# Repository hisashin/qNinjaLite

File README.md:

# Open Source $50 qLAMP machine qNinja

# $300 Real Time PCR and LAMP machine "[qNinja](https://github.com/hisashin/qNinja)" is also available

## Reference Links
- [qNinja portal](https://qninja.hisa.dev)

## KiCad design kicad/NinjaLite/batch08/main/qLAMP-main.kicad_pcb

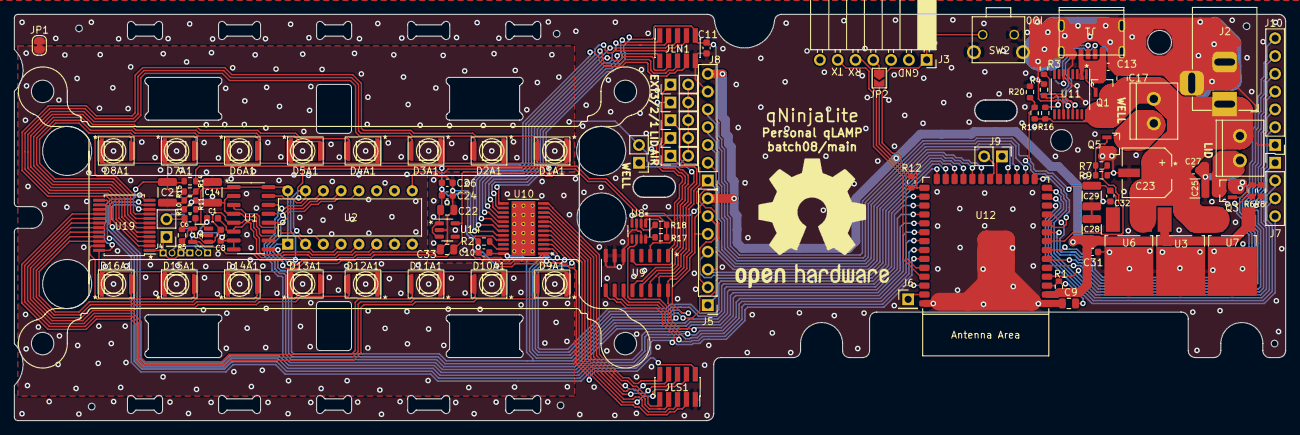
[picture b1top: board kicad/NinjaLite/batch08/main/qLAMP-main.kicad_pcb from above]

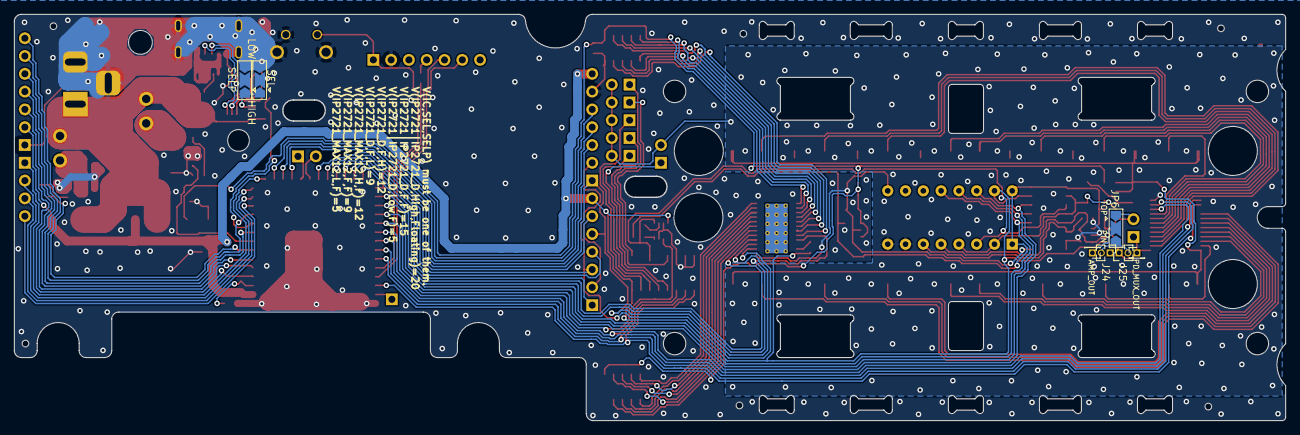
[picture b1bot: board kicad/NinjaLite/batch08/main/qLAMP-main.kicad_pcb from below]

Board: 2 copper layers, 181.5 x 58.0 mm, 102 parts (7 on the bottom side), 104 nets.

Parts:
C1, C10, C11, C24, C27, C31, C32: 0.1uF; C_0603_1608Metric
C2, C14, C25, C28, C29: 22uF; C_1210_3225Metric
C6: 5pF; C_0603_1608Metric
C8: DNP; C_0603_1608Metric
C9: 10uF; C_0805_2012Metric
C13: 1uF(<=20V); C_0603_1608Metric
C17: 10uF(<=20V); C_0805_2012Metric
C22, C33: 4.7uF; C_0805_2012Metric
C23: 100uF; 35TZV100M6.3X8
C26: 0.01uF; C_0603_1608Metric
D1A1, D2A1, D3A1, D4A1, D5A1, D6A1, D7A1, D8A1, D9A1, D10A1, D11A1, D12A1, D13A1, D14A1, D15A1, D16A1: D_Photo; SFH2200_2201_2240
HLID1: Screw_Terminal_01x02; TB_SeeedOPL_320110028
HWELL1: Screw_Terminal_01x02; TB_SeeedOPL_320110028
J1: ALI_USB
J2: Barrel_Jack_Switch; BarrelJack_Horizontal
J3: Conn_01x07_Male; PinSocket_1x07_P2.54mm_Horizontal
J4: Conn_01x02_Male; PinHeader_1x02_P2.54mm_Vertical
J5, J8: Conn_01x07_Male; PinHeader_1x07_P2.54mm_Vertical
J6: Conn_01x01_Pin; PinHeader_1x01_P2.54mm_Vertical
J7: Conn_01x04_Male; PinHeader_1x04_P2.54mm_Vertical
J9: Conn_01x02_Pin; PinHeader_1x02_P2.54mm_Vertical
J10: Conn_01x07_Pin; PinHeader_1x07_P2.54mm_Vertical
J13, J16: Conn_01x01_Male; PinHeader_1x01_P1.27mm_Vertical
J24, J25: Conn_01x02_Male; PinHeader_1x02_P1.27mm_Vertical
JLN1: Conn_01x10_Male; PinSocket_2x05_P1.27mm_Vertical_SMD
JLS1: Conn_01x10_Male; PinSocket_2x05_P1.27mm_Vertical_SMD
JP1: SolderJumper_2_Bridged; SolderJumper-2_P1.3mm_Bridged_RoundedPad1.0x1.5mm
JP2: Jumper_2_Bridged; SolderJumper-2_P1.3mm_Open_TrianglePad1.0x1.5mm
JP6, JP9, JP10: Jumper_3_Open; SolderJumper-3_P2.0mm_Open_TrianglePad1.0x1.5mm
Q1, Q3, Q5: Q_NMOS_GSD; SOT95P240X112-3N
R1, R12, R15, R16, R19: 100k; R_0603_1608Metric
R2: 3.3k; R_0603_1608Metric
R3, R4: 5.1k; R_0603_1608Metric
R5: 10M; R_0603_1608Metric
R6, R7: 150; R_0603_1608Metric
R8, R9: 47k; R_0603_1608Metric
R10, R11, R18: 47k_HP; R_0603_1608Metric
R14, R20: 10k; R_0603_1608Metric
R17: 10k_HP; R_0603_1608Metric
SW2: TACTILE_4; SW_TH_Tactile_alps_SKHHLPA010
TAIR1: Conn_01x02_Male; PinHeader_1x02_P2.54mm_Vertical
TEXT1, TEXT2, TEXT3: Conn_01x02_Male; PinHeader_1x02_P2.54mm_Vertical
TLID1: Conn_01x02_Male; PinHeader_1x02_P2.54mm_Vertical
TWELL1: Conn_01x02_Male; PinHeader_1x02_P2.54mm_Vertical
U1: NAU7802; SOIC-16_3.9x9.9mm_P1.27mm
U2: NAU7802; DIP-16_W7.62mm
U3: BD433M5FP-CE2; REG_TO252-3
U4: LMP7717MF_NOPB; SOT-23-5
U6: BA178M05FP-E2; REG_TO252-3
U7: BD433M5FP-CE2; REG_TO252-3-INV
U8: TS12A12511DCNR; SOT-23-8-8.3mil
U9: SN74LV4051A; SOIC-16_3.9x9.9mm_P1.27mm
U10: TLC5929; HTSSOP-24-1EP_4.4x7.8mm_P0.65mm_EP3.4x7.8mm_Mask2.4x4.68mm_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
U11: IP2721; TSSOP-16_4.4x5mm_P0.65mm
U12: ESP32-­S3-­WROOM­-1; ESP32-S3-WROOM-1
U14: TCR3DF33,LM(CT; SOT-23-5
U19: CD74HC4067M96; SSOP-24_5.3x8.2mm_P0.65mm-0.83mil

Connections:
3V3A: C33.1, R10.1, R17.1, R18.1, U1.1 (REFP), U1.16 (AVDD), U2.1 (REFP), U2.16 (AVDD), U4.3 (IN+), U14.5 (VOUT)
3V3D: C10.1, C28.1, C31.1, J5.7, J8.7, J10.2, JP2.2 (B), R1.2, R12.2, U1.15 (DVDD), U2.15 (DVDD), U3.2 (VOUT), U4.5 (V+), U7.2 (VOUT), U8.4 (V+), U9.16 (VCC), U10.24 (VCC), U12.2 (3V3)
5V: C11.1, C22.1, C24.1, C26.1, C29.1, C32.1, JLN1.9, JLS1.2, R14.1, U6.2 (VOUT), U14.1 (VIN), U14.3 (SHDN)
/BOOTMODE: J3.1, R12.1, SW2.1, U12.27 (IO0)
/IO1: J6.1, U12.39 (IO1)
/IO4: J10.3, U12.4 (IO4)
/IO5: J10.4, U12.5 (IO5)
/IO6: J10.5, U12.6 (IO6)
/IO11: J9.1, U12.19 (IO11)
/IO12: J9.2, U12.20 (IO12)
/IO16: J10.6, U12.9 (IO16)
/IO18: J10.7, U12.11 (IO18)
/LCD_CS: J8.5, U12.16 (IO46)
/LCD_DC/RS: J8.3, U12.18 (IO10)
/LCD_RESET: J8.4, U12.17 (IO9)
/LID_HEATER: R6.2, U12.7 (IO7)
/MISO: J5.2, J5.6, U12.22 (IO14)
/Photo/AMP_OUT: C8.1, J16.1, JP6.2 (C), U1.5 (VIN2P), U2.5 (VIN2P), U4.1 (OUT)
/Photo/VBG: C1.1, U1.6 (VBG), U2.6 (VBG)
/PhotoLED/N_LED_OUT1: JLN1.8, U10.20 (OUT15)
/PhotoLED/N_LED_OUT2: JLN1.7, U10.19 (OUT14)
/PhotoLED/N_LED_OUT3: JLN1.6, U10.18 (OUT13)
/PhotoLED/N_LED_OUT4: JLN1.5, U10.17 (OUT12)
/PhotoLED/N_LED_OUT5: JLN1.4, U10.16 (OUT11)
/PhotoLED/N_LED_OUT6: JLN1.3, U10.15 (OUT10)
/PhotoLED/N_LED_OUT7: JLN1.2, U10.14 (OUT9)
/PhotoLED/N_LED_OUT8: JLN1.1, U10.13 (OUT8)
/PhotoLED/S_LED_OUT1: JLS1.3, U10.5 (OUT0)
/PhotoLED/S_LED_OUT2: JLS1.4, U10.6 (OUT1)
/PhotoLED/S_LED_OUT3: JLS1.5, U10.7 (OUT2)
/PhotoLED/S_LED_OUT4: JLS1.6, U10.8 (OUT3)
/PhotoLED/S_LED_OUT5: JLS1.7, U10.9 (OUT4)
/PhotoLED/S_LED_OUT6: JLS1.8, U10.10 (OUT5)
/PhotoLED/S_LED_OUT7: JLS1.9, U10.11 (OUT6)
/PhotoLED/S_LED_OUT8: JLS1.10, U10.12 (OUT7)
/PhotoMUX/N_PD_OUT1: D1A1.2 (A), U19.2 (I7)
/PhotoMUX/N_PD_OUT3: D2A1.2 (A), U19.3 (I6)
/PhotoMUX/N_PD_OUT5: D3A1.2 (A), U19.4 (I5)
/PhotoMUX/N_PD_OUT7: D4A1.2 (A), U19.5 (I4)
/PhotoMUX/N_PD_OUT9: D5A1.2 (A), U19.6 (I3)
/PhotoMUX/N_PD_OUT11: D6A1.2 (A), U19.7 (I2)
/PhotoMUX/N_PD_OUT13: D7A1.2 (A), U19.8 (I1)
/PhotoMUX/N_PD_OUT15: D8A1.2 (A), U19.9 (I0)
/PhotoMUX/S_PD_OUT1: D9A1.2 (A), U19.16 (I15)
/PhotoMUX/S_PD_OUT3: D10A1.2 (A), U19.17 (I14)
/PhotoMUX/S_PD_OUT5: D11A1.2 (A), U19.18 (I13)
/PhotoMUX/S_PD_OUT7: D12A1.2 (A), U19.19 (I12)
/PhotoMUX/S_PD_OUT9: D13A1.2 (A), U19.20 (I11)
/PhotoMUX/S_PD_OUT11: D14A1.2 (A), U19.21 (I10)
/PhotoMUX/S_PD_OUT13: D15A1.2 (A), U19.22 (I9)
/PhotoMUX/S_PD_OUT15: D16A1.2 (A), U19.23 (I8)
/Power/SEL: JP9.2 (C), U11.11 (SEL)
/Power/SELP: JP10.2 (C), U11.6 (SELP)
/Power/VIN: C13.1, J1.A9 (VBUS), J1.B9 (VBUS), Q1.3 (D), U11.2 (VIN)
/RXD: J3.5, U12.36 (IO44/RXD0)
/SD_CLK: J7.4, U12.12 (IO8)
/SD_CS: J7.1, U12.15 (IO3)
/SD_MISO: J7.3, U12.13 (IO19)
/SD_MOSI: J7.2, U12.14 (IO20)
/TP_CS: J5.4, U12.24 (IO47)
/TP_IRQ: J5.1, U12.25 (IO48)
/TXD: J3.6, U12.37 (IO43/TXD0)
/WELL_HEATER: R7.2, U12.8 (IO15)
DIVIDED: C14.1, R10.2, R11.1, U1.2 (VIN1N), U1.4 (VIN2N), U2.2 (VIN1N), U2.4 (VIN2N)
GNDA: C1.2, C2.2, C8.2, C14.2, JP1.2 (B), R11.2, R15.2, TAIR1.2, TEXT1.2, TEXT2.2, TEXT3.2, TLID1.2, TWELL1.2, U1.7 (REFN), U1.8 (AVSS), U2.7 (REFN), U2.8 (AVSS), U4.2 (V-), U19.12 (GND), U19.15 (*E)
GNDD: C9.2, C10.2, C11.2, C13.2, C17.2, C22.2, C23.2, C24.2, C25.2, C26.2, C27.2, C28.2, C29.2, C31.2, C32.2, C33.2, J1.A12 (GND), J1.B12 (GND), J1.S1 (SHELD1), J1.S2 (SHELD2), J1.S3 (SHELD3), J1.S4 (SHELD4), J2.2, J2.3, J3.2, J8.6, J10.1, JLN1.10, JLS1.1, JP1.1 (A), JP9.3 (B), JP10.3 (B), Q3.2 (S), Q5.2 (S), R2.2, R3.1, R4.1, R8.1, R9.1, R20.2, SW2.2, SW2.GND, U1.9 (DVSS), U2.9 (DVSS), U3.3 (GND), U6.3 (GND), U7.3 (GND), U8.3 (GND), U8.7 (V-), U9.6 (INH), U9.7 (GND), U9.8 (GND), U10.1 (GND), U11.5 (GND), U12.1 (GND), U12.40 (GND), U12.41 (GND), U14.2 (GND)
I2C_SCL: U1.13 (SCLK), U2.13 (SCLK), U12.30 (IO37)
I2C_SDA: U1.14 (SDIO), U2.14 (SDIO), U12.31 (IO38)
LED_BLANK: U10.21 (BLANK), U12.28 (IO35)
LED_LAT: U10.4 (LAT), U12.26 (IO45)
MOSI: J5.3, J8.2, U10.2 (SIN), U12.23 (IO21)
MUX_S0: U9.11 (A), U12.33 (IO40), U19.10 (S0)
MUX_S1: U9.10 (B), U12.35 (IO42), U19.11 (S1)
MUX_S2: U9.9 (C), U12.38 (IO2), U19.14 (S2)
MUX_S3: U12.34 (IO41), U19.13 (S3)
NAU_DRDY: U1.12 (DRDY), U2.12 (DRDY), U12.29 (IO36)
unnamed: HLID1.2, Q3.3 (D)
unnamed: HWELL1.2, Q5.3 (D)
unnamed: J1.A5 (CC1), R3.2, U11.13 (CC1)
unnamed: J1.B5 (CC2), R4.2, U11.12 (CC2)
unnamed: J3.4, JP2.1 (A)
unnamed: C6.1, J4.2, JP6.1 (A), R5.2
unnamed: J24.2, J25.2, JP6.3 (B)
unnamed: JP9.1 (A), JP10.1 (A), R16.1
unnamed: Q1.1 (G), U11.1 (VBUSG)
unnamed: Q3.1 (G), R6.1, R8.2
unnamed: Q5.1 (G), R7.1, R9.2
unnamed: R18.2, U8.2 (NC)
unnamed: R17.2, U8.8 (NO)
unnamed: R2.1, U10.23 (IREF)
unnamed: C9.1, R1.1, U12.3 (EN)
PD_MUX_OUT: C6.2, J4.1, J13.1, J24.1, J25.1, R5.1, U4.4 (IN-), U19.1 (COMMONINPUT/OUTPUT)
SCLK: J5.5, J8.1, U10.3 (SCLK), U12.21 (IO13)
THERM_AIR: TAIR1.1, U9.14 (Y1)
THERM_EXT1: TEXT1.1, U9.15 (Y2)
THERM_EXT2: TEXT2.1, U9.1 (Y4)
THERM_EXT3: TEXT3.1, U9.5 (Y5)
THERM_LID: TLID1.1, U9.12 (Y3)
THERM_MUX_OUT: U1.3 (VIN1P), U2.3 (VIN1P), U8.1 (COM), U9.3 (COM)
THERM_R_SWITCH: U8.6 (IN), U12.32 (IO39)
THERM_WELL: TWELL1.1, U9.13 (Y0)
VCC: C17.1, C23.1, C25.1, C27.1, HLID1.1, HWELL1.1, J2.1, Q1.2 (S), R16.2, R19.1, U3.1 (VIN), U6.1 (VIN), U7.1 (VIN), U11.16 (VBUS)
VIN_SENSE: R19.2, R20.1, U12.10 (IO17)
VOPT: C2.1, D1A1.1 (K), D2A1.1 (K), D3A1.1 (K), D4A1.1 (K), D5A1.1 (K), D6A1.1 (K), D7A1.1 (K), D8A1.1 (K), D9A1.1 (K), D10A1.1 (K), D11A1.1 (K), D12A1.1 (K), D13A1.1 (K), D14A1.1 (K), D15A1.1 (K), D16A1.1 (K), R14.2, R15.1, U19.24 (VCC)

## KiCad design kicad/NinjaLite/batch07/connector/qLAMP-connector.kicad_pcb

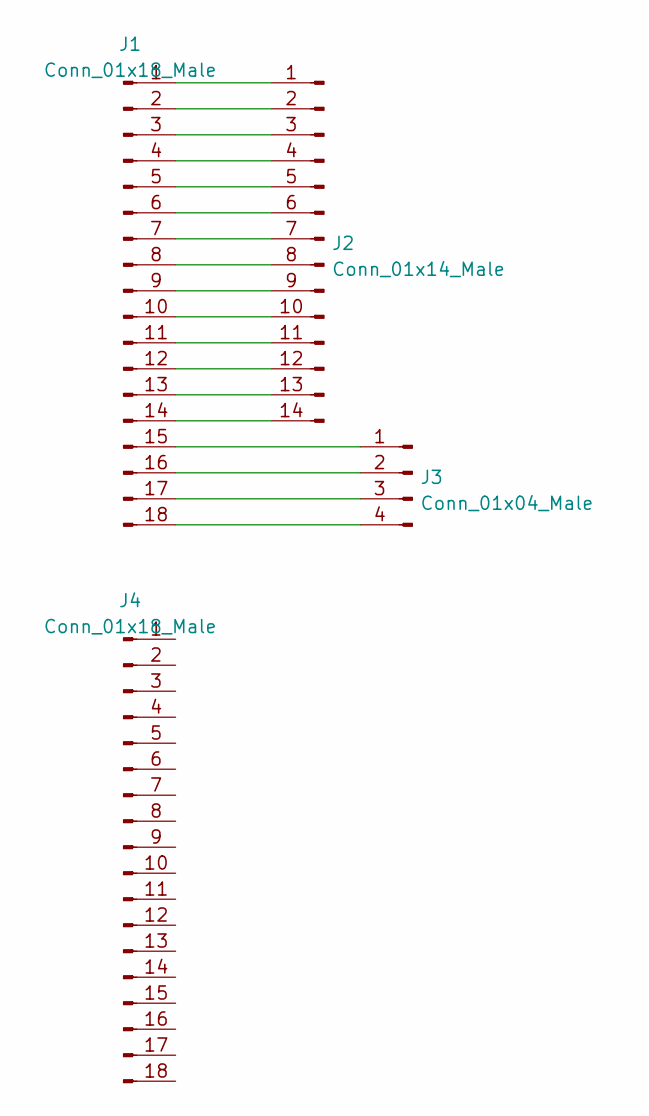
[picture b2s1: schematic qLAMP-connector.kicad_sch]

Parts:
J1: Conn_01x18_Male; PinSocket_2x09_P2.54mm_Vertical
J2: Conn_01x14_Male; PinSocket_1x14_P2.54mm_Vertical
J3: Conn_01x04_Male; PinSocket_1x04_P2.54mm_Vertical
J4: Conn_01x18_Male; PinSocket_2x09_P1.27mm_Vertical

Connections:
unnamed: J1.1, J2.1
unnamed: J1.2, J2.2
unnamed: J1.3, J2.3
unnamed: J1.4, J2.4
unnamed: J1.5, J2.5
unnamed: J1.6, J2.6
unnamed: J1.7, J2.7
unnamed: J1.8, J2.8
unnamed: J1.9, J2.9
unnamed: J1.10, J2.10
unnamed: J1.11, J2.11
unnamed: J1.12, J2.12
unnamed: J1.13, J2.13
unnamed: J1.14, J2.14
unnamed: J1.15, J3.1
unnamed: J1.16, J3.2
unnamed: J1.17, J3.3
unnamed: J1.18, J3.4

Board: 2 copper layers, 4 parts (0 on the bottom side), 18 nets, no tracks yet.

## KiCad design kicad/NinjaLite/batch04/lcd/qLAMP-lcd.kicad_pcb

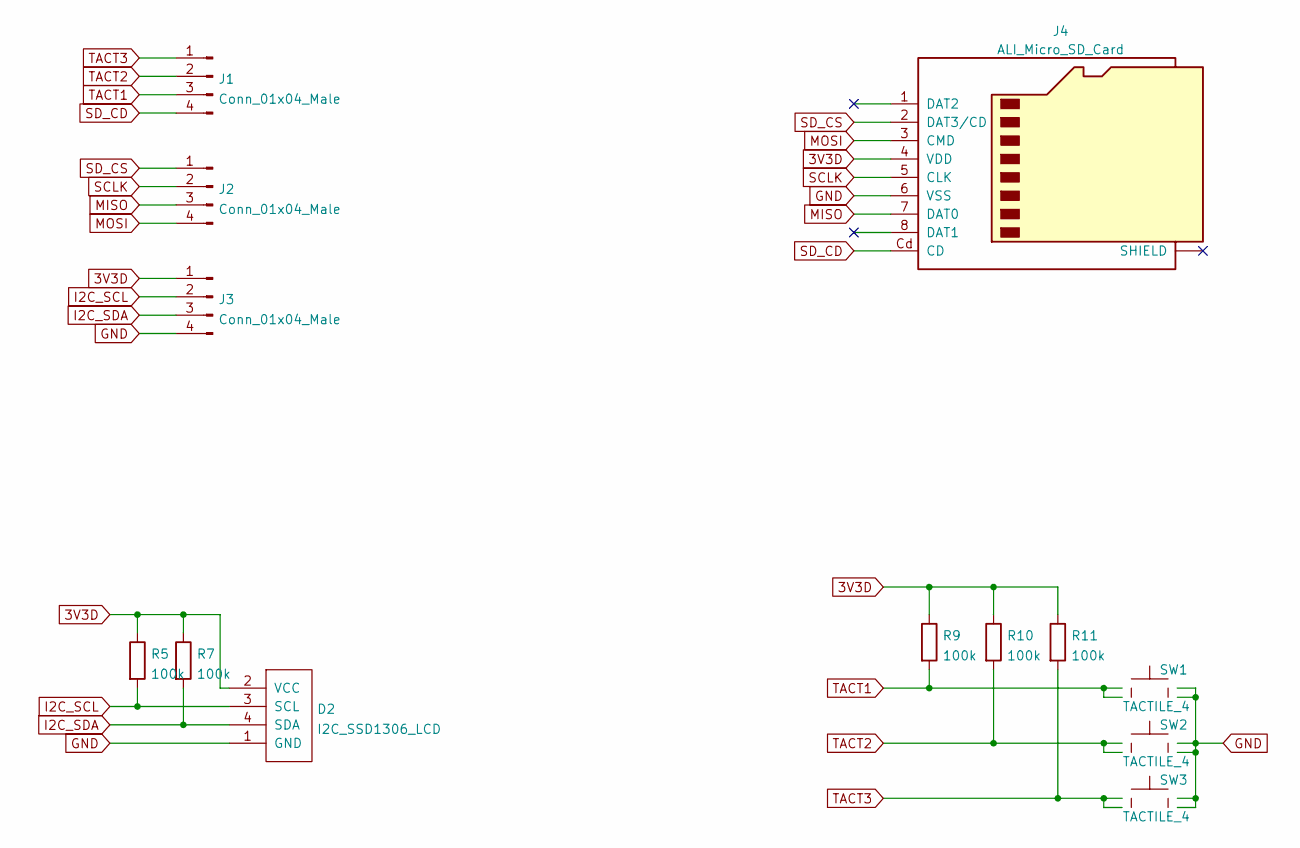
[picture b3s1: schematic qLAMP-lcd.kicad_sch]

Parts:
D2: I2C_SSD1306_LCD; ALI_I2C_LCD
J1, J2, J3: Conn_01x04_Male; PinHeader_1x04_P2.54mm_Vertical
J4: ALI_Micro_SD_Card; ALI_microSD
R5, R7, R9, R10, R11: 100k; R_0603_1608Metric
SW1, SW2, SW3: TACTILE_4; SW_TH_Tactile_Omron_B3F-10xx

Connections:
3V3D: D2.2 (VCC), J3.1, J4.4 (VDD), R5.1, R7.1, R9.1, R10.1, R11.1
GND: D2.1 (GND), J3.4, J4.6 (VSS), SW1.3, SW1.4, SW2.3, SW2.4, SW3.3, SW3.4
I2C_SCL: D2.3 (SCL), J3.2, R5.2
I2C_SDA: D2.4 (SDA), J3.3, R7.2
MISO: J2.3, J4.7 (DAT0)
MOSI: J2.4, J4.3 (CMD)
SCLK: J2.2, J4.5 (CLK)
SD_CD: J1.4, J4.Cd (CD)
SD_CS: J2.1, J4.2 (DAT3/CD)
TACT1: J1.3, R9.2, SW1.1, SW1.2
TACT2: J1.2, R10.2, SW2.1, SW2.2
TACT3: J1.1, R11.2, SW3.1, SW3.2

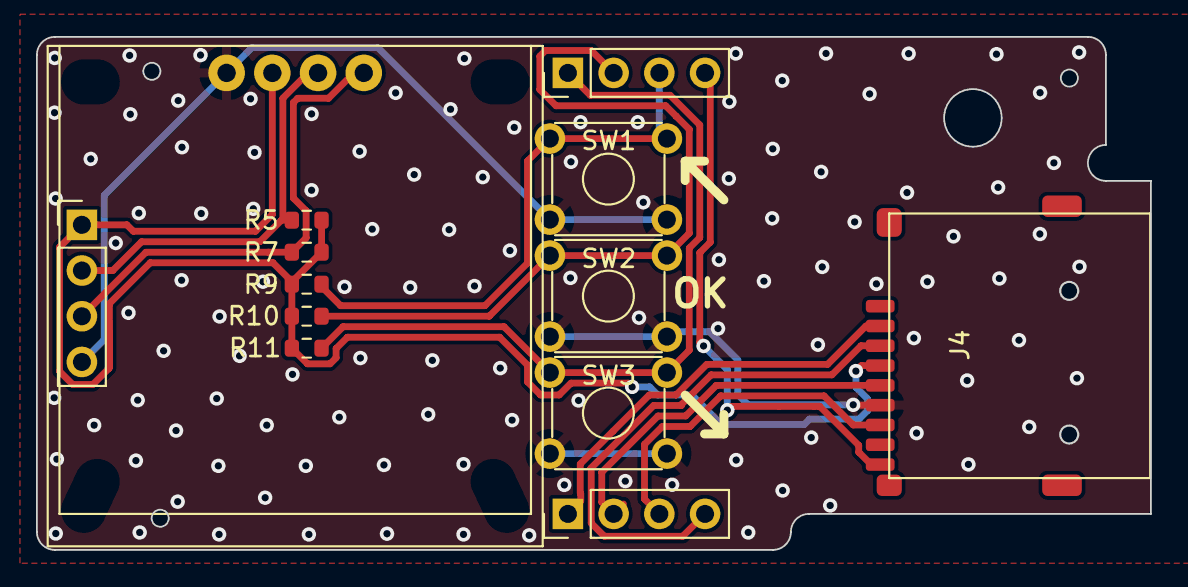
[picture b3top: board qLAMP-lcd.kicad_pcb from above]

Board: 2 copper layers, 61.9 x 28.5 mm, 13 parts (0 on the bottom side), 12 nets.

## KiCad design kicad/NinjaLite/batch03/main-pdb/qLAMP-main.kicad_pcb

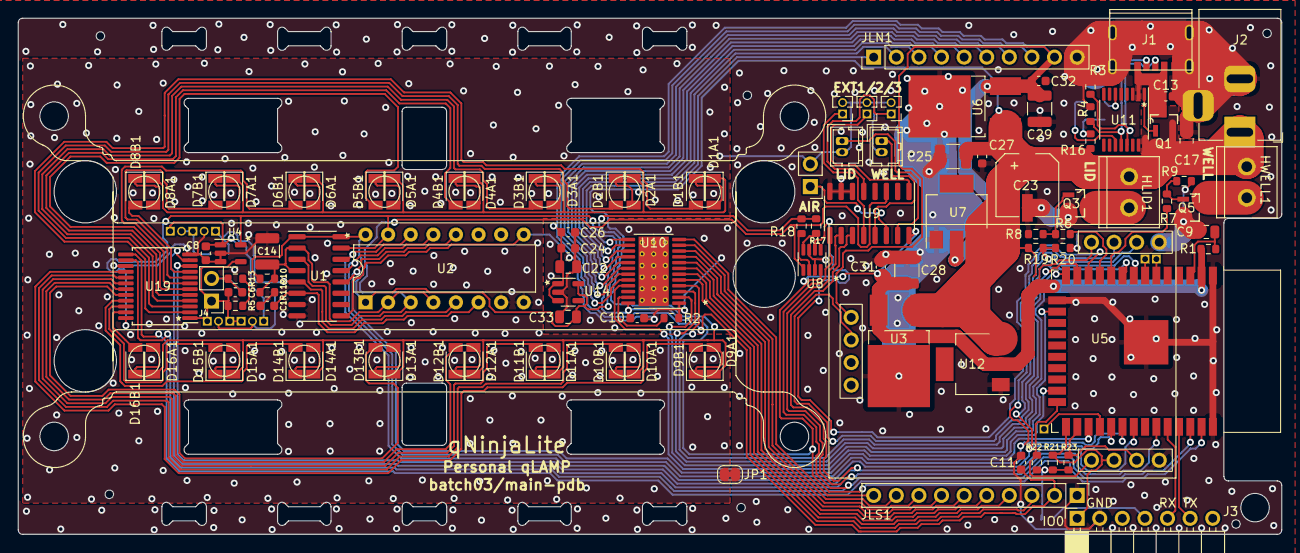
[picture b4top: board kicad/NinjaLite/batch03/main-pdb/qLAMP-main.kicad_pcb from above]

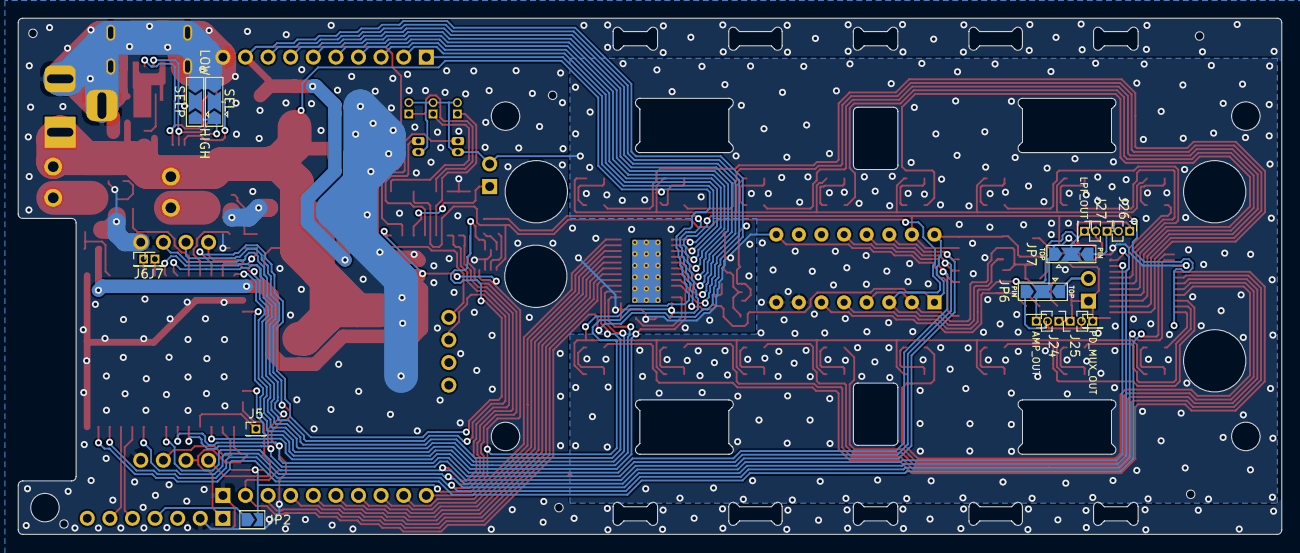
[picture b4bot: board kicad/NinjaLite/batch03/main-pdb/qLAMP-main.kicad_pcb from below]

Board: 2 copper layers, 142.0 x 58.0 mm, 120 parts (15 on the bottom side), 110 nets.

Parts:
C1, C10, C11, C24, C27, C31, C32: 0.1uF; C_0603_1608Metric
C6: 5pF; C_0603_1608Metric
C8: DNP; C_0603_1608Metric
C9: 10uF; C_0805_2012Metric
C13: 1uF(<=20V); C_0603_1608Metric
C14, C25, C28, C29: 22uF; C_1210_3225Metric
C17: 10uF(<=20V); C_0805_2012Metric
C22, C33: 4.7uF; C_0805_2012Metric
C23: 100uF; 35TZV100M6.3X8
C26: 0.01uF; C_0603_1608Metric
D1A1, D1B1, D2A1, D2B1, D3A1, D3B1, D4A1, D4B1, D5A1, D5B1, D6A1, D6B1, D7A1, D7B1, D8A1, D8B1, D9A1, D9B1, D10A1, D10B1, D11A1, D11B1, D12A1, D12B1, D13A1, D13B1, D14A1, D14B1, D15A1, D15B1, D16A1, D16B1: D_Photo; D_1206
HLID1: Screw_Terminal_01x02; TB_SeeedOPL_320110028
HWELL1: Screw_Terminal_01x02; TB_SeeedOPL_320110028
J1: ALI_USB
J2: Barrel_Jack_Switch; BarrelJack_Horizontal
J3: Conn_01x07_Male; PinSocket_1x07_P2.54mm_Horizontal
J4: Conn_01x02_Male; PinHeader_1x02_P2.54mm_Vertical
J5, J6, J7: Conn_01x01_Male; Pin_Header_Straight_1x01_Pitch1.27mm
J13, J16, J23: Conn_01x01_Male; PinHeader_1x01_P1.27mm_Vertical
J24, J25, J26, J27: Conn_01x02_Male; PinHeader_1x02_P1.27mm_Vertical
JLN1: Conn_01x10_Male; PinHeader_1x10_P2.54mm_Vertical
JLS1: Conn_01x10_Male; PinHeader_1x10_P2.54mm_Vertical
JP1: SolderJumper_2_Bridged; SolderJumper-2_P1.3mm_Bridged_RoundedPad1.0x1.5mm
JP2: Jumper_2_Bridged; SolderJumper-2_P1.3mm_Open_TrianglePad1.0x1.5mm
JP6, JP7, JP9, JP10: Jumper_3_Open; SolderJumper-3_P2.0mm_Open_TrianglePad1.0x1.5mm
Q1, Q3, Q5: Q_NMOS_GSD; SOT95P240X112-3N
R1, R16, R19, R21, R22, R23: 100k; R_0603_1608Metric
R2: 3.3k; R_0603_1608Metric
R3, R4: 5.1k; R_0603_1608Metric
R5, R13: 10M; R_0603_1608Metric
R6, R7: 150; R_0603_1608Metric
R8, R9: 47k; R_0603_1608Metric
R10, R11, R18: 47k_HP; R_0603_1608Metric
R17: 10k_HP; R_0603_1608Metric
R20: 10k; R_0603_1608Metric
TAIR1: Conn_01x02_Male; PinHeader_1x02_P2.54mm_Vertical
TEXT1, TEXT2, TEXT3: Conn_01x02_Male; Pin_Header_Straight_1x02_Pitch1.27mm
TLID1: Conn_01x02_Male; Hirose_DF13-02P-1.25DSA_1x02_P1.25mm_Vertical
TWELL1: Conn_01x02_Male; Hirose_DF13-02P-1.25DSA_1x02_P1.25mm_Vertical
U1: NAU7802; SOIC-16_3.9x9.9mm_P1.27mm
U2: NAU7802; DIP-16_W7.62mm
U3: BD433M5FP-CE2; REG_TO252-3
U4: LMP7717MF_NOPB; SOT-23-5
U5: ESP32-WROOM-32
U6: BA178M05FP-E2; REG_TO252-3
U7, U12: LD1086DTTR; SOT-223
U8: TS12A12511DCNR; SOT-23-8
U9: SN74LV4051A; SOIC-16_3.9x9.9mm_P1.27mm
U10: TLC5929; HTSSOP-24-1EP_4.4x7.8mm_P0.65mm_EP3.4x7.8mm_Mask2.4x4.68mm_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
U11: IP2721; TSSOP-16_4.4x5mm_P0.65mm
U14: TCR3DF33,LM(CT; SOT-23-5
U17: LITE_LCD
U19: CD74HC4067M96; SSOP-24_5.3x8.2mm_P0.65mm

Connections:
3V3A: C33.1, R10.1, R17.1, R18.1, U1.1 (REFP), U1.16 (AVDD), U2.1 (REFP), U2.16 (AVDD), U14.5 (VOUT)
3V3D: C10.1, C28.1, C31.1, JP2.2 (B), R1.2, R21.2, R22.2, R23.2, U1.15 (DVDD), U2.15 (DVDD), U3.2 (VOUT), U4.5 (V+), U5.2 (VDD), U8.4 (V+), U9.16 (VCC), U10.24 (VCC), U12.2 (OUT), U17.1 (VCC), U19.24 (VCC)
5V: C11.1, C22.1, C24.1, C26.1, C29.1, C32.1, JLN1.9, JLS1.2, U6.2 (VOUT), U7.2 (OUT), U14.1 (VIN), U14.3 (SHDN), U17.9 (VCCL)
/LID_HEATER: R6.2, U5.11 (IO26)
/Photo/AMP_OUT: C8.1, J16.1, J26.1, JP6.2 (C), JP7.1 (A), U4.1 (OUT)
/Photo/LPF_OUT: J23.1, JP7.2 (C), U1.5 (VIN2P), U2.5 (VIN2P)
/Photo/VBG: C1.1, U1.6 (VBG), U2.6 (VBG)
/PhotoLED/N_LED_OUT1: JLN1.8, U10.20 (OUT15)
/PhotoLED/N_LED_OUT2: JLN1.7, U10.19 (OUT14)
/PhotoLED/N_LED_OUT3: JLN1.6, U10.18 (OUT13)
/PhotoLED/N_LED_OUT4: JLN1.5, U10.17 (OUT12)
/PhotoLED/N_LED_OUT5: JLN1.4, U10.16 (OUT11)
/PhotoLED/N_LED_OUT6: JLN1.3, U10.15 (OUT10)
/PhotoLED/N_LED_OUT7: JLN1.2, U10.14 (OUT9)
/PhotoLED/N_LED_OUT8: JLN1.1, U10.13 (OUT8)
/PhotoLED/S_LED_OUT1: JLS1.3, U10.5 (OUT0)
/PhotoLED/S_LED_OUT2: JLS1.4, U10.6 (OUT1)
/PhotoLED/S_LED_OUT3: JLS1.5, U10.7 (OUT2)
/PhotoLED/S_LED_OUT4: JLS1.6, U10.8 (OUT3)
/PhotoLED/S_LED_OUT5: JLS1.7, U10.9 (OUT4)
/PhotoLED/S_LED_OUT6: JLS1.8, U10.10 (OUT5)
/PhotoLED/S_LED_OUT7: JLS1.9, U10.11 (OUT6)
/PhotoLED/S_LED_OUT8: JLS1.10, U10.12 (OUT7)
/PhotoMUX/N_PD_OUT1: D1B1.2 (A), U19.2 (I7)
/PhotoMUX/N_PD_OUT3: D2B1.2 (A), U19.3 (I6)
/PhotoMUX/N_PD_OUT5: D3B1.2 (A), U19.4 (I5)
/PhotoMUX/N_PD_OUT7: D4B1.2 (A), U19.5 (I4)
/PhotoMUX/N_PD_OUT9: D5B1.2 (A), U19.6 (I3)
/PhotoMUX/N_PD_OUT11: D6B1.2 (A), U19.7 (I2)
/PhotoMUX/N_PD_OUT13: D7B1.2 (A), U19.8 (I1)
/PhotoMUX/N_PD_OUT15: D8B1.2 (A), U19.9 (I0)
/PhotoMUX/S_PD_OUT1: D9B1.2 (A), U19.16 (I15)
/PhotoMUX/S_PD_OUT3: D10B1.2 (A), U19.17 (I14)
/PhotoMUX/S_PD_OUT5: D11B1.2 (A), U19.18 (I13)
/PhotoMUX/S_PD_OUT7: D12B1.2 (A), U19.19 (I12)
/PhotoMUX/S_PD_OUT9: D13B1.2 (A), U19.20 (I11)
/PhotoMUX/S_PD_OUT11: D14B1.2 (A), U19.21 (I10)
/PhotoMUX/S_PD_OUT13: D15B1.2 (A), U19.22 (I9)
/PhotoMUX/S_PD_OUT15: D16B1.2 (A), U19.23 (I8)
/Power/SEL: JP9.2 (C), U11.11 (SEL)
/Power/SELP: JP10.2 (C), U11.6 (SELP)
/Power/VIN: C13.1, J1.A9 (VBUS), J1.B9 (VBUS), Q1.3 (D), U11.2 (VIN)
/RXD: J3.5, U5.34 (RXD0/IO3)
/TXD: J3.6, U5.35 (TXD0/IO1)
/WELL_HEATER: R7.2, U5.10 (IO25)
DIVIDED: C14.1, R10.2, R11.1, U1.2 (VIN1N), U1.4 (VIN2N), U2.2 (VIN1N), U2.4 (VIN2N)
GNDA: C1.2, C8.2, C14.2, J27.2, JP1.2 (B), R11.2, TAIR1.2, TEXT1.2, TEXT2.2, TEXT3.2, TLID1.2, TWELL1.2, U1.7 (REFN), U1.8 (AVSS), U2.7 (REFN), U2.8 (AVSS), U4.2 (V-), U4.3 (IN+), U19.12 (GND), U19.15 (*E)
GNDD: C9.2, C10.2, C11.2, C13.2, C17.2, C22.2, C23.2, C24.2, C25.2, C26.2, C27.2, C28.2, C29.2, C31.2, C32.2, C33.2, J1.A12 (GND), J1.B12 (GND), J1.S1 (SHELD1), J1.S2 (SHELD2), J1.S3 (SHELD3), J1.S4 (SHELD4), J2.2, J2.3, J3.2, JLN1.10, JLS1.1, JP1.1 (A), JP9.3 (B), JP10.3 (B), Q3.2 (S), Q5.2 (S), R2.2, R3.1, R4.1, R8.1, R9.1, R20.2, U1.9 (DVSS), U2.9 (DVSS), U3.3 (GND), U5.1 (GND), U5.15 (GND), U5.38 (GND), U5.39 (GND), U6.3 (GND), U7.1 (ADJ/GND), U8.3 (GND), U8.7 (V-), U9.6 (INH), U9.7 (GND), U9.8 (GND), U10.1 (GND), U11.5 (GND), U12.1 (ADJ/GND), U14.2 (GND), U17.4 (GND), U17.8 (GND)
I2C_SCL: U1.13 (SCLK), U2.13 (SCLK), U5.30 (IO18), U17.2 (SCL)
I2C_SDA: U1.14 (SDIO), U2.14 (SDIO), U5.29 (IO5), U17.3 (SDA)
LED: U5.9 (IO33), U17.10 (LED_R)
LED_BLANK: U5.23 (IO15), U10.21 (BLANK)
LED_LAT: U5.13 (IO14), U10.4 (LAT)
LED_SPI_MOSI: U5.16 (IO13), U10.2 (SIN)
LED_SPI_SCLK: U5.14 (IO12), U10.3 (SCLK)
MUX_S0: U5.31 (IO19), U9.11 (A), U19.10 (S0)
MUX_S1: U5.33 (IO21), U9.10 (B), U19.11 (S1)
MUX_S2: U5.36 (IO22), U9.9 (C), U19.14 (S2)
MUX_S3: U5.37 (IO23), U19.13 (S3)
NAU_DRDY: U1.12 (DRDY), U2.12 (DRDY), U5.27 (IO16)
unnamed: C6.1, J4.2, JP6.1 (A), R13.2
unnamed: C9.1, R1.1, U5.3 (EN)
unnamed: D1A1.2 (A), D1B1.1 (K)
unnamed: D2A1.2 (A), D2B1.1 (K)
unnamed: D3A1.2 (A), D3B1.1 (K)
unnamed: D4A1.2 (A), D4B1.1 (K)
unnamed: D5A1.2 (A), D5B1.1 (K)
unnamed: D6A1.2 (A), D6B1.1 (K)
unnamed: D7A1.2 (A), D7B1.1 (K)
unnamed: D8A1.2 (A), D8B1.1 (K)
unnamed: D9A1.2 (A), D9B1.1 (K)
unnamed: D10A1.2 (A), D10B1.1 (K)
unnamed: D11A1.2 (A), D11B1.1 (K)
unnamed: D12A1.2 (A), D12B1.1 (K)
unnamed: D13A1.2 (A), D13B1.1 (K)
unnamed: D14A1.2 (A), D14B1.1 (K)
unnamed: D15A1.2 (A), D15B1.1 (K)
unnamed: D16A1.2 (A), D16B1.1 (K)
unnamed: HLID1.2, Q3.3 (D)
unnamed: HWELL1.2, Q5.3 (D)
unnamed: J1.A5 (CC1), R3.2, U11.13 (CC1)
unnamed: J1.B5 (CC2), R4.2, U11.12 (CC2)
unnamed: J3.4, JP2.1 (A)
unnamed: J5.1, U5.28 (IO17)
unnamed: J6.1, U5.6 (IO34)
unnamed: J7.1, U5.7 (IO35)
unnamed: J24.2, J25.2, JP6.3 (B)
unnamed: J26.2, J27.1, JP7.3 (B)
unnamed: JP9.1 (A), JP10.1 (A), R16.1
unnamed: Q1.1 (G), U11.1 (VBUSG)
unnamed: Q3.1 (G), R6.1, R8.2
unnamed: Q5.1 (G), R7.1, R9.2
unnamed: R2.1, U10.23 (IREF)
unnamed: R5.2, R13.1
unnamed: R17.2, U8.8 (NO)
unnamed: R18.2, U8.2 (NC)
PD_MUX_OUT: C6.2, J4.1, J13.1, J24.1, J25.1, R5.1, U4.4 (IN-), U19.1 (COMMONINPUT/OUTPUT)
TACT1: R23.1, U5.26 (IO4), U17.7 (TACT1)
TACT2: J3.1, R21.1, U5.25 (IO0), U17.6 (TACT2)
TACT3: R22.1, U5.24 (IO2), U17.5 (TACT3)
THERM_AIR: TAIR1.1, U9.14 (Y1)
THERM_EXT1: TEXT1.1, U9.12 (Y3)
THERM_EXT2: TEXT2.1, U9.1 (Y4)
THERM_EXT3: TEXT3.1, U9.5 (Y5)
THERM_LID: TLID1.1, U9.15 (Y2)
THERM_MUX_OUT: U1.3 (VIN1P), U2.3 (VIN1P), U8.1 (COM), U9.3 (COM)
THERM_R_SWITCH: U5.12 (IO27), U8.6 (IN)
THERM_WELL: TWELL1.1, U9.13 (Y0)
VCC: C17.1, C23.1, C25.1, C27.1, D1A1.1 (K), D2A1.1 (K), D3A1.1 (K), D4A1.1 (K), D5A1.1 (K), D6A1.1 (K), D7A1.1 (K), D8A1.1 (K), D9A1.1 (K), D10A1.1 (K), D11A1.1 (K), D12A1.1 (K), D13A1.1 (K), D14A1.1 (K), D15A1.1 (K), D16A1.1 (K), HLID1.1, HWELL1.1, J2.1, Q1.2 (S), R16.2, R19.1, U3.1 (VIN), U6.1 (VIN), U7.3 (IN), U11.16 (VBUS), U12.3 (IN)
VIN_SENSE: R19.2, R20.1, U5.8 (IO32)

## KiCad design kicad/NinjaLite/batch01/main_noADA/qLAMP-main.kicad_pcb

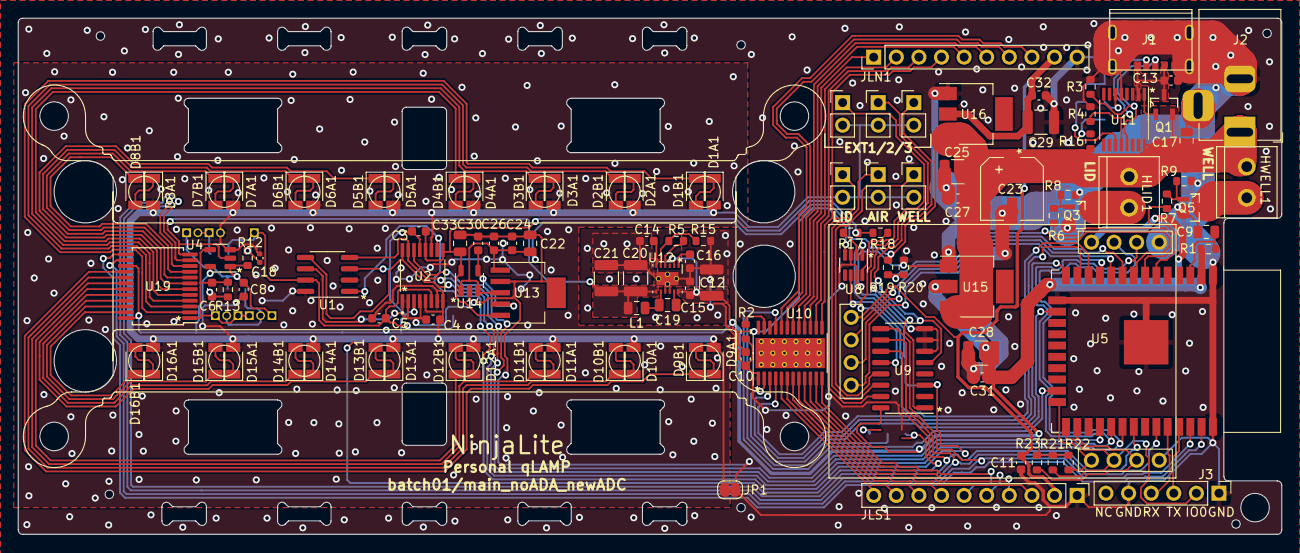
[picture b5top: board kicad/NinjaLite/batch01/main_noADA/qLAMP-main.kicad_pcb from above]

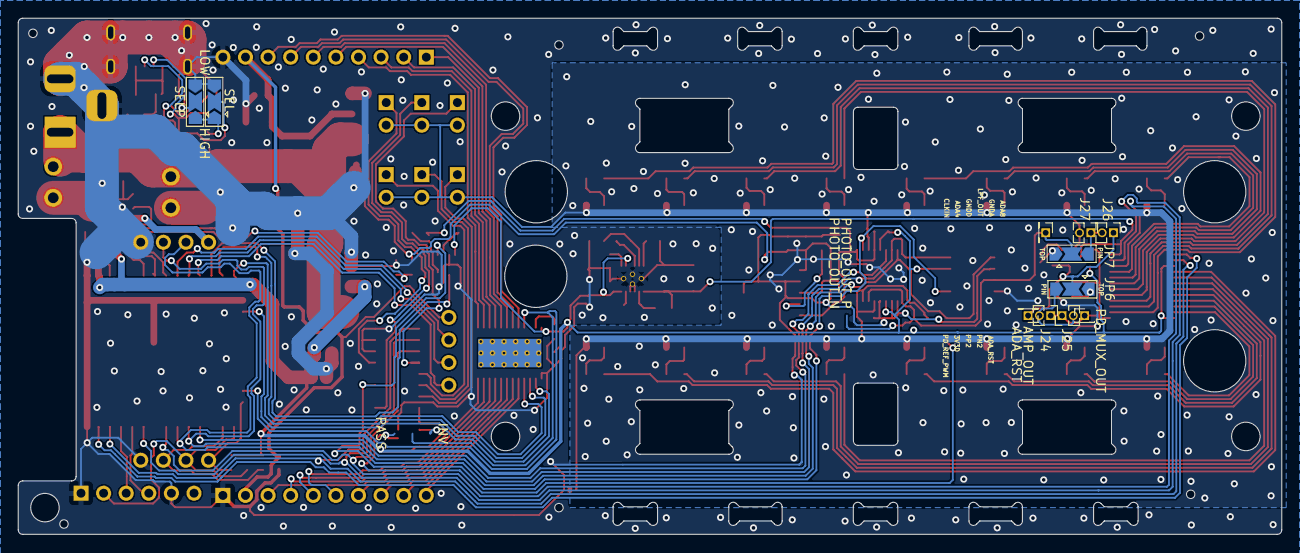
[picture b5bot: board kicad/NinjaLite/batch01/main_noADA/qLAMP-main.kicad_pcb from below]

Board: 2 copper layers, 142.0 x 58.0 mm, 126 parts (11 on the bottom side), 114 nets.

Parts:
C3, C4, C5, C8, C10, C11, C24, C27, C31, C32: 0.1uF; C_0603_1608Metric
C6: DNP(<1pF); C_0603_1608Metric
C9, C19: 10uF; C_0805_2012Metric
C12, C20, C21, C25, C28, C29: 22uF; C_1210_3225Metric
C13: 1uF(<=20V); C_0603_1608Metric
C14, C15, C16: 1uF; C_0603_1608Metric
C17: 10uF(<=20V); C_0805_2012Metric
C18: 330pF; C_0402_1005Metric
C22, C33: 4.7uF; C_0805_2012Metric
C23: 100uF; 35TZV100M6.3X8
C26: 0.01uF; C_0603_1608Metric
C30: 100pF; C_0603_1608Metric
D1A1, D1B1, D2A1, D2B1, D3A1, D3B1, D4A1, D4B1, D5A1, D5B1, D6A1, D6B1, D7A1, D7B1, D8A1, D8B1, D9A1, D9B1, D10A1, D10B1, D11A1, D11B1, D12A1, D12B1, D13A1, D13B1, D14A1, D14B1, D15A1, D15B1, D16A1, D16B1: D_Photo; D_1206
HLID1: Screw_Terminal_01x02; TB_SeeedOPL_320110028
HWELL1: Screw_Terminal_01x02; TB_SeeedOPL_320110028
J1: ALI_USB
J2: Barrel_Jack_Switch; BarrelJack_Horizontal
J3: Conn_01x06_Male; PinHeader_1x06_P2.54mm_Vertical
J13, J16, J23: Conn_01x01_Male; PinHeader_1x01_P1.27mm_Vertical
J24, J25, J26, J27: Conn_01x02_Male; PinHeader_1x02_P1.27mm_Vertical
JLN1: Conn_01x10_Male; PinHeader_1x10_P2.54mm_Vertical
JLS1: Conn_01x10_Male; PinHeader_1x10_P2.54mm_Vertical
JP1: SolderJumper_2_Bridged; SolderJumper-2_P1.3mm_Bridged_RoundedPad1.0x1.5mm
JP6, JP7, JP9, JP10: Jumper_3_Open; SolderJumper-3_P2.0mm_Open_TrianglePad1.0x1.5mm
L1: 2.2uH; C_0805_2012Metric
Q1, Q3, Q5: Q_NMOS_GSD; SOT95P240X112-3N
R1, R16, R19, R21, R22, R23: 100k; R_0603_1608Metric
R2: 0; R_0603_1608Metric
R3, R4: 5.1k; R_0603_1608Metric
R5: 39k; R_0603_1608Metric
R6, R7: 150; R_0603_1608Metric
R8, R9: 47k; R_0603_1608Metric
R12, R20: 10k; R_0603_1608Metric
R13: 10M; R_0603_1608Metric
R15: 150k; R_0603_1608Metric
R17: 10k_HP; R_0603_1608Metric
R18: 47k_HP; R_0603_1608Metric
TAIR1: Conn_01x02_Male; PinHeader_1x02_P2.54mm_Vertical
TEXT1, TEXT2, TEXT3: Conn_01x02_Male; PinHeader_1x02_P2.54mm_Vertical
TLID1: Conn_01x02_Male; PinHeader_1x02_P2.54mm_Vertical
TWELL1: Conn_01x02_Male; PinHeader_1x02_P2.54mm_Vertical
U1: MCP3426; SOIC-8_3.9x4.9mm_P1.27mm
U2: ADS1219IPWR; ADS122C04IPWR
U4: LMP7717MF_NOPB; SOT-23-5
U5: ESP32-WROOM-32
U8: TS12A12511DCNR; SOT-23-8
U9: SN74LV4051A; SOIC-16_3.9x9.9mm_P1.27mm
U10: TLC5929; HTSSOP-24-1EP_4.4x7.8mm_P0.65mm_EP3.4x7.8mm_Mask2.4x4.68mm_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
U11: IP2721; TSSOP-16_4.4x5mm_P0.65mm
U12: TPS63710DRRR
U13: MCP1755T-3302E_DC; SOT-223-6
U14: MCP1755T-3302E_OT; SOT-23-5
U15: CJT1117-3.3; SOT-223
U16: CJT1117-5.0; SOT-223
U17: LITE_LCD
U19: CD74HC4067M96; SSOP-24_5.3x8.2mm_P0.65mm

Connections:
3V3A: C3.1, C33.1, R17.1, R18.1, U2.9 (REFP), U2.12 (AVDD), U13.5 (VOUT), U14.5 (VOUT)
3V3D: C3.2, C10.1, C12.1, C15.1, C28.1, C31.1, R1.2, R21.2, R22.2, R23.2, U1.3 (VDD), U2.3 (RESET_N), U2.13 (DVDD), U4.5 (V+), U5.2 (VDD), U8.4 (V+), U9.16 (VCC), U10.24 (VCC), U12.2 (EN), U12.12 (VIN), U15.2 (OUTPUT), U17.1 (VCC), U19.15 (*E), U19.24 (VCC)
5V: C11.1, C29.1, C32.1, JLN1.9, JLS1.2, U16.2 (OUTPUT), U17.9 (VCCL)
12V: C17.1, C22.1, C23.1, C24.1, C25.1, C26.1, C27.1, HLID1.1, HWELL1.1, J2.1, Q1.2 (S), R16.2, R19.1, U11.16 (VBUS), U13.1 (VIN), U13.3 (SHDN), U14.1 (VIN), U14.3 (SHDN), U15.3 (INPUT), U16.3 (INPUT)
-1V: C20.1, C21.1, L1.2, U4.2 (V-), U12.7 (VOUT), U19.12 (GND)
/LID_HEATER: R6.2, U5.7 (IO35)
/Photo/AMP_OUT: C8.1, J16.1, J26.1, JP6.2 (C), R12.2, U4.1 (OUT)
/Photo/LPF_OUT: C5.2, J23.1, JP7.2 (C), U1.7 (CH2+), U2.6 (AIN3)
/PhotoLED/N_LED_OUT1: JLN1.8, U10.20 (OUT15)
/PhotoLED/N_LED_OUT2: JLN1.7, U10.19 (OUT14)
/PhotoLED/N_LED_OUT3: JLN1.6, U10.18 (OUT13)
/PhotoLED/N_LED_OUT4: JLN1.5, U10.17 (OUT12)
/PhotoLED/N_LED_OUT5: JLN1.4, U10.13 (OUT8)
/PhotoLED/N_LED_OUT6: JLN1.3, U10.14 (OUT9)
/PhotoLED/N_LED_OUT7: JLN1.2, U10.15 (OUT10)
/PhotoLED/N_LED_OUT8: JLN1.1, U10.16 (OUT11)
/PhotoLED/S_LED_OUT1: JLS1.3, U10.9 (OUT4)
/PhotoLED/S_LED_OUT2: JLS1.4, U10.10 (OUT5)
/PhotoLED/S_LED_OUT3: JLS1.5, U10.11 (OUT6)
/PhotoLED/S_LED_OUT4: JLS1.6, U10.12 (OUT7)
/PhotoLED/S_LED_OUT5: JLS1.7, U10.8 (OUT3)
/PhotoLED/S_LED_OUT6: JLS1.8, U10.7 (OUT2)
/PhotoLED/S_LED_OUT7: JLS1.9, U10.6 (OUT1)
/PhotoLED/S_LED_OUT8: JLS1.10, U10.5 (OUT0)
/PhotoMUX/N_PD_OUT1: D1B1.1 (K), U19.2 (I7)
/PhotoMUX/N_PD_OUT3: D2B1.1 (K), U19.3 (I6)
/PhotoMUX/N_PD_OUT5: D3B1.1 (K), U19.4 (I5)
/PhotoMUX/N_PD_OUT7: D4B1.1 (K), U19.5 (I4)
/PhotoMUX/N_PD_OUT9: D5B1.1 (K), U19.6 (I3)
/PhotoMUX/N_PD_OUT11: D6B1.1 (K), U19.7 (I2)
/PhotoMUX/N_PD_OUT13: D7B1.1 (K), U19.8 (I1)
/PhotoMUX/N_PD_OUT15: D8B1.1 (K), U19.9 (I0)
/PhotoMUX/S_PD_OUT1: D9B1.1 (K), U19.16 (I15)
/PhotoMUX/S_PD_OUT3: D10B1.1 (K), U19.17 (I14)
/PhotoMUX/S_PD_OUT5: D11B1.1 (K), U19.18 (I13)
/PhotoMUX/S_PD_OUT7: D12B1.1 (K), U19.19 (I12)
/PhotoMUX/S_PD_OUT9: D13B1.1 (K), U19.20 (I11)
/PhotoMUX/S_PD_OUT11: D14B1.1 (K), U19.21 (I10)
/PhotoMUX/S_PD_OUT13: D15B1.1 (K), U19.22 (I9)
/PhotoMUX/S_PD_OUT15: D16B1.1 (K), U19.23 (I8)
/Power/PWRGD: C30.1, U13.4 (PWRGD), U14.4 (PWRGD)
/Power/SEL: JP9.2 (C), U11.11 (SEL)
/Power/SELP: JP10.2 (C), U11.6 (SELP)
/Power/VIN: C13.1, J1.A9 (VBUS), J1.B9 (VBUS), Q1.3 (D), U11.2 (VIN)
/RXD: J3.4, U5.34 (RXD0/IO3)
/TXD: J3.3, U5.35 (TXD0/IO1)
/WELL_HEATER: R7.2, U5.6 (IO34)
ADC_DRDY: U2.14 (DRDY_N), U5.28 (IO17)
GNDA: C4.1, C5.1, C8.2, C18.2, D1A1.2 (A), D2A1.2 (A), D3A1.2 (A), D4A1.2 (A), D5A1.2 (A), D6A1.2 (A), D7A1.2 (A), D8A1.2 (A), D9A1.2 (A), D10A1.2 (A), D11A1.2 (A), D12A1.2 (A), D13A1.2 (A), D14A1.2 (A), D15A1.2 (A), D16A1.2 (A), J27.2, JP1.2 (B), TAIR1.2, TEXT1.2, TEXT2.2, TEXT3.2, TLID1.2, TWELL1.2, U1.2 (CH1-), U1.8 (CH2-), U2.5 (AVSS), U2.7 (AIN2), U2.8 (REFN), U2.11 (AIN0), U4.3 (IN+)
GNDD: C4.2, C9.2, C10.2, C11.2, C12.2, C13.2, C14.2, C15.2, C16.2, C17.2, C20.2, C21.2, C22.2, C23.2, C24.2, C25.2, C26.2, C27.2, C28.2, C29.2, C30.2, C31.2, C32.2, C33.2, J1.A12 (GND), J1.B12 (GND), J1.S1 (SHELD1), J1.S2 (SHELD2), J1.S3 (SHELD3), J1.S4 (SHELD4), J2.2, J2.3, J3.1, J3.5, JLN1.10, JLS1.1, JP1.1 (A), JP9.3 (B), JP10.3 (B), Q3.2 (S), Q5.2 (S), R2.2, R3.1, R4.1, R8.1, R9.1, R15.2, R20.2, U1.6 (VSS), U2.1 (A0), U2.2 (A1), U2.4 (DGND), U5.1 (GND), U5.15 (GND), U5.38 (GND), U5.39 (GND), U8.3 (GND), U8.7 (V-), U9.6 (INH), U9.7 (GND), U9.8 (GND), U10.1 (GND), U11.5 (GND), U12.9 (GND), U12.10 (GND), U12.13 (PAD), U13.2 (GND), U13.6 (EP), U14.2 (GND), U15.1 (ADJ/GND), U16.1 (ADJ/GND), U17.4 (GND), U17.8 (GND)
I2C_SCL: U1.5 (SCL), U2.16 (SCL), U5.30 (IO18), U17.2 (SCL)
I2C_SDA: U1.4 (SDA), U2.15 (SDA), U5.29 (IO5), U17.3 (SDA)
LED_B: U5.11 (IO26), U17.12 (LED_B)
LED_BLANK: U5.23 (IO15), U10.21 (BLANK)
LED_G: U5.10 (IO25), U17.11 (LED_G)
LED_LAT: U5.13 (IO14), U10.4 (LAT)
LED_R: U5.9 (IO33), U17.10 (LED_R)
LED_SPI_MOSI: U5.16 (IO13), U10.2 (SIN)
LED_SPI_SCLK: U5.14 (IO12), U10.3 (SCLK)
MUX_S0: U5.31 (IO19), U9.11 (A), U19.10 (S0)
MUX_S1: U5.33 (IO21), U9.10 (B), U19.11 (S1)
MUX_S2: U5.36 (IO22), U9.9 (C), U19.14 (S2)
MUX_S3: U5.37 (IO23), U19.13 (S3)
unnamed: C6.1, JP6.1 (A), R13.2
unnamed: C9.1, R1.1, U5.3 (EN)
unnamed: C14.1, U12.6 (CAP)
unnamed: C16.1, U12.1 (VAUX)
unnamed: C18.1, JP7.1 (A), R12.1
unnamed: C19.1, U12.11 (CP)
unnamed: C19.2, L1.1, U12.8 (SW)
unnamed: D1A1.1 (K), D1B1.2 (A)
unnamed: D2A1.1 (K), D2B1.2 (A)
unnamed: D3A1.1 (K), D3B1.2 (A)
unnamed: D4A1.1 (K), D4B1.2 (A)
unnamed: D5A1.1 (K), D5B1.2 (A)
unnamed: D6A1.1 (K), D6B1.2 (A)
unnamed: D7A1.1 (K), D7B1.2 (A)
unnamed: D8A1.1 (K), D8B1.2 (A)
unnamed: D9A1.1 (K), D9B1.2 (A)
unnamed: D10A1.1 (K), D10B1.2 (A)
unnamed: D11A1.1 (K), D11B1.2 (A)
unnamed: D12A1.1 (K), D12B1.2 (A)
unnamed: D13A1.1 (K), D13B1.2 (A)
unnamed: D14A1.1 (K), D14B1.2 (A)
unnamed: D15A1.1 (K), D15B1.2 (A)
unnamed: D16A1.1 (K), D16B1.2 (A)
unnamed: HLID1.2, Q3.3 (D)
unnamed: HWELL1.2, Q5.3 (D)
unnamed: J1.A5 (CC1), R3.2, U11.13 (CC1)
unnamed: J1.B5 (CC2), R4.2, U11.12 (CC2)
unnamed: J24.2, J25.2, JP6.3 (B)
unnamed: J26.2, J27.1, JP7.3 (B)
unnamed: JP9.1 (A), JP10.1 (A), R16.1
unnamed: Q1.1 (G), U11.1 (VBUSG)
unnamed: Q3.1 (G), R6.1, R8.2
unnamed: Q5.1 (G), R7.1, R9.2
unnamed: R2.1, U10.23 (IREF)
unnamed: R5.1, U12.4 (VREF)
unnamed: R5.2, R15.1, U12.5 (FB)
unnamed: R17.2, U8.8 (NO)
unnamed: R18.2, U8.2 (NC)
PD_MUX_OUT: C6.2, J13.1, J24.1, J25.1, R13.1, U4.4 (IN-), U19.1 (COMMONINPUT/OUTPUT)
TACT1: R23.1, U5.26 (IO4), U17.7 (TACT1)
TACT2: J3.2, R21.1, U5.25 (IO0), U17.6 (TACT2)
TACT3: R22.1, U5.24 (IO2), U17.5 (TACT3)
THERM_AIR: TAIR1.1, U9.14 (Y1)
THERM_EXT1: TEXT1.1, U9.12 (Y3)
THERM_EXT2: TEXT2.1, U9.1 (Y4)
THERM_EXT3: TEXT3.1, U9.5 (Y5)
THERM_LID: TLID1.1, U9.15 (Y2)
THERM_MUX_OUT: U1.1 (CH1+), U2.10 (AIN1), U8.1 (COM), U9.3 (COM)
THERM_R_SWITCH: U5.12 (IO27), U8.6 (IN)
THERM_WELL: TWELL1.1, U9.13 (Y0)
VIN_SENSE: R19.2, R20.1, U5.8 (IO32)

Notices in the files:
parts and their libraries:
Copyright 2021 Accelerated Designs. All rights reserved.
